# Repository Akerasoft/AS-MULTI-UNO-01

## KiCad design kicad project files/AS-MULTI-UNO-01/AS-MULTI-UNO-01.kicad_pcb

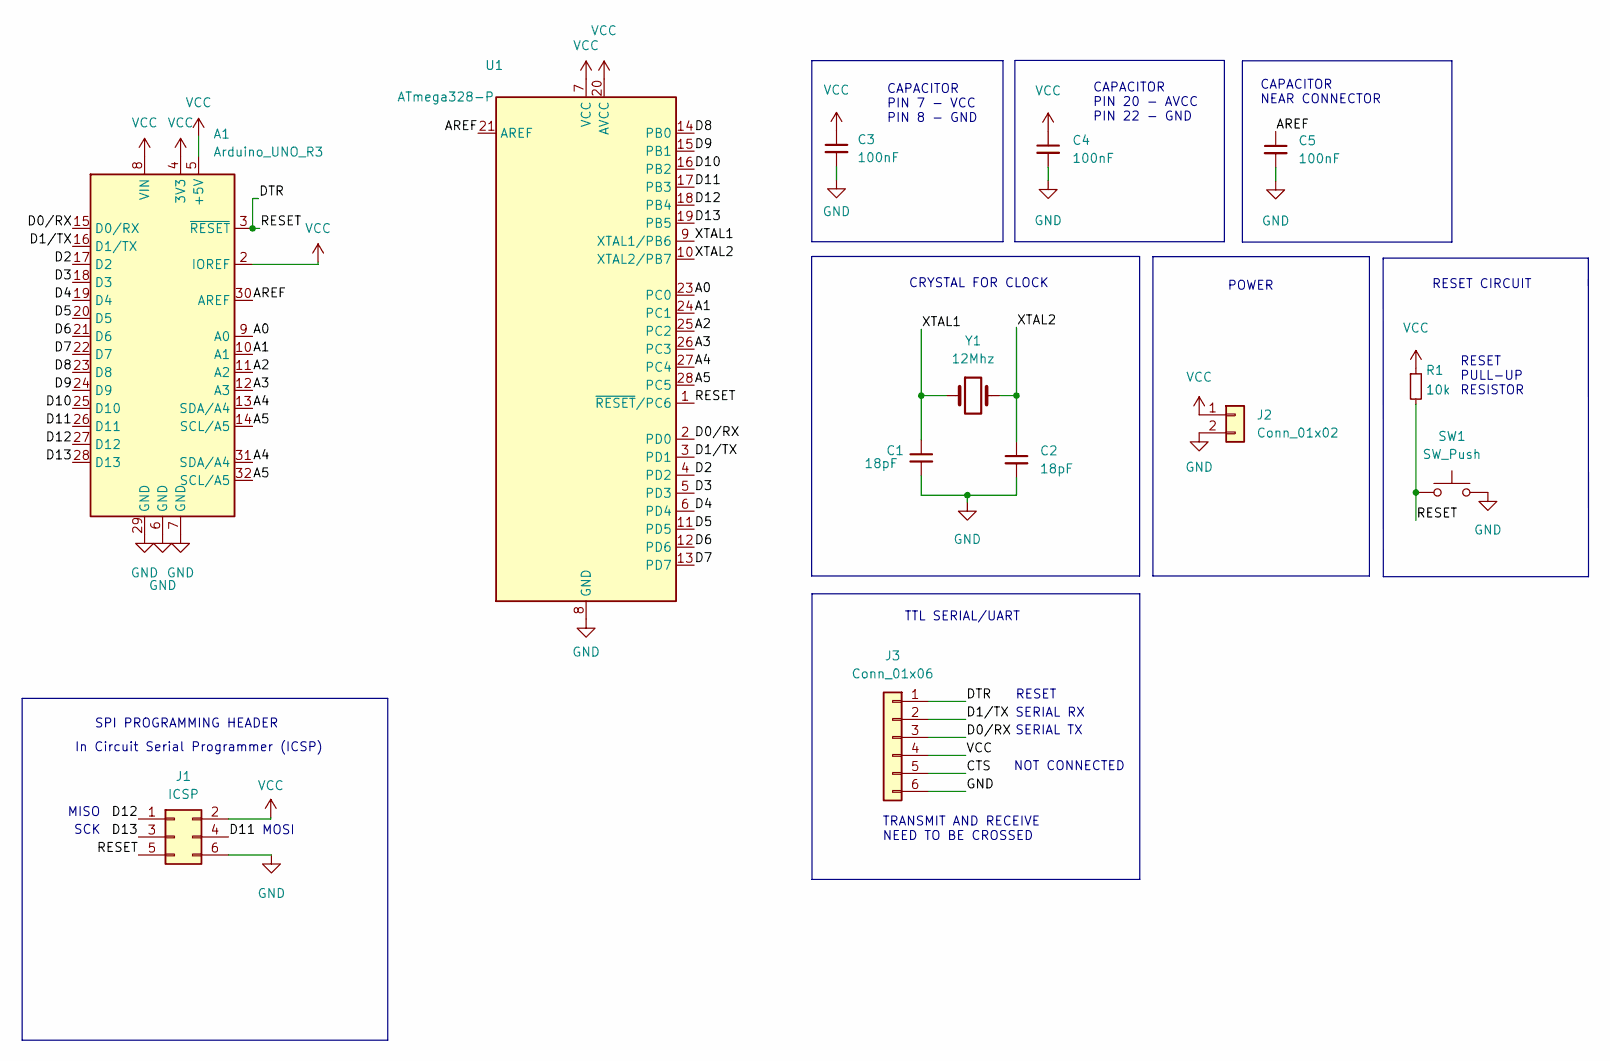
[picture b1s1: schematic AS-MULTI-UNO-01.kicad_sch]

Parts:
A1: Arduino_UNO_R3; Arduino_UNO_R3_WithMountingHoles
C1, C2: 18pF; C_Disc_D3.0mm_W2.0mm_P2.50mm
C3, C4, C5: 100nF; C_Disc_D3.0mm_W2.0mm_P2.50mm
J1: ICSP; PinHeader_2x03_P2.54mm_Vertical
J2: Conn_01x02; JST_XH_S2B-XH-A_1x02_P2.50mm_Horizontal
J3: Conn_01x06; PinHeader_1x06_P2.54mm_Horizontal
R1: 10k; R_Axial_DIN0207_L6.3mm_D2.5mm_P7.62mm_Horizontal
SW1: SW_Push; SW_PUSH_6mm_H4.3mm
U1: ATmega328-P; DIP-28_W7.62mm_Socket
Y1: 12Mhz; Crystal_HC49-4H_Vertical

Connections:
/A0: A1.9 (A0), U1.23 (PC0)
/A1: A1.10 (A1), U1.24 (PC1)
/A2: A1.11 (A2), U1.25 (PC2)
/A3: A1.12 (A3), U1.26 (PC3)
/A4: A1.13 (SDA/A4), A1.31 (SDA/A4), U1.27 (PC4)
/A5: A1.14 (SCL/A5), A1.32 (SCL/A5), U1.28 (PC5)
/AREF: A1.30 (AREF), C5.1, U1.21 (AREF)
/CTS: J3.5
/D0/RX: A1.15 (D0/RX), J3.3, U1.2 (PD0)
/D1/TX: A1.16 (D1/TX), J3.2, U1.3 (PD1)
/D2: A1.17 (D2), U1.4 (PD2)
/D3: A1.18 (D3), U1.5 (PD3)
/D4: A1.19 (D4), U1.6 (PD4)
/D5: A1.20 (D5), U1.11 (PD5)
/D6: A1.21 (D6), U1.12 (PD6)
/D7: A1.22 (D7), U1.13 (PD7)
/D8: A1.23 (D8), U1.14 (PB0)
/D9: A1.24 (D9), U1.15 (PB1)
/D10: A1.25 (D10), U1.16 (PB2)
/D11: A1.26 (D11), J1.4, U1.17 (PB3)
/D12: A1.27 (D12), J1.1, U1.18 (PB4)
/D13: A1.28 (D13), J1.3, U1.19 (PB5)
/DTR: A1.3 (~RESET), J1.5, J3.1, R1.2, SW1.1, U1.1 (~RESET/PC6)
/XTAL1: C1.1, U1.9 (XTAL1/PB6), Y1.1
/XTAL2: C2.1, U1.10 (XTAL2/PB7), Y1.2
GND: A1.6 (GND), A1.7 (GND), A1.29 (GND), C1.2, C2.2, C3.2, C4.2, C5.2, J1.6, J2.2, J3.6, SW1.2, U1.8 (GND), U1.22 (GND)
VCC: A1.2 (IOREF), A1.4 (3V3), A1.5 (+5V), A1.8 (VIN), C3.1, C4.1, J1.2, J2.1, J3.4, R1.1, U1.7 (VCC), U1.20 (AVCC)

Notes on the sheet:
MOSI
SPI PROGRAMMING HEADER
TTL SERIAL/UART
SCK
RESET CIRCUIT
CRYSTAL FOR CLOCK
CAPACITOR NEAR CONNECTOR
CAPACITOR PIN 7 - VCC PIN 8 - GND
RESET PULL-UP RESISTOR
TRANSMIT AND RECEIVE NEED TO BE CROSSED
POWER
SERIAL RX
NOT CONNECTED
In Circuit Serial Programmer (ICSP)
CAPACITOR PIN 20 - AVCC PIN 22 - GND
MISO
SERIAL TX
RESET

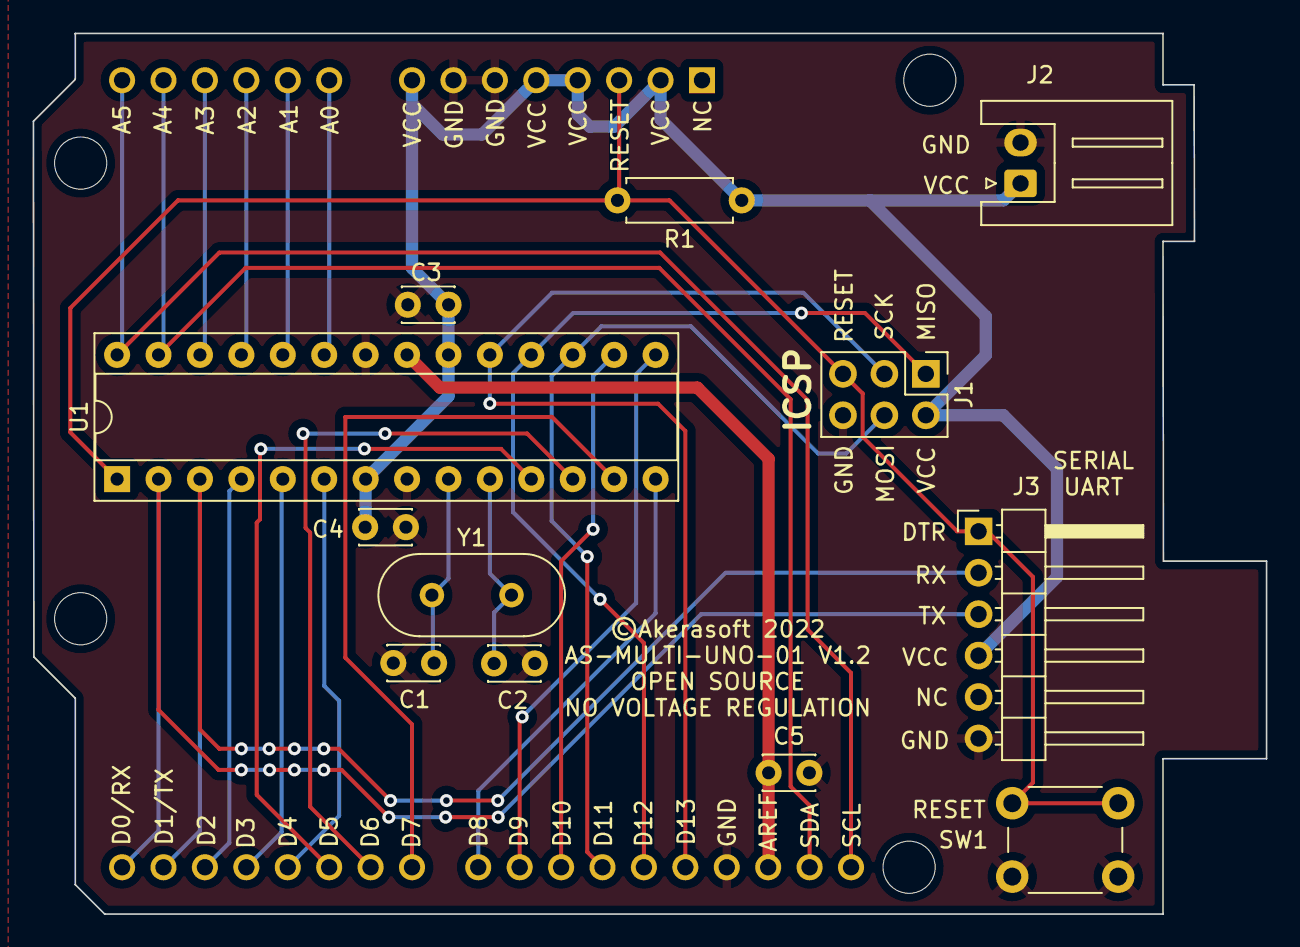
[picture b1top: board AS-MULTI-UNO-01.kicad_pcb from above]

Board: 2 copper layers, 75.6 x 54.0 mm, 13 parts (1 on the bottom side), 26 nets.

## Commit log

2022-12-20 fix gerber files
2022-12-24 Fix BOM

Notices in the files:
kicad project files/AS-MULTI-UNO-01/AS-MULTI-UNO-01.kicad_pcb:
©Akerasoft 2022
kicad project files/AS-MULTI-UNO-01/AS-MULTI-UNO-01.kicad_sch:
License: Creative Commons Attribution 4.0 International Public License
